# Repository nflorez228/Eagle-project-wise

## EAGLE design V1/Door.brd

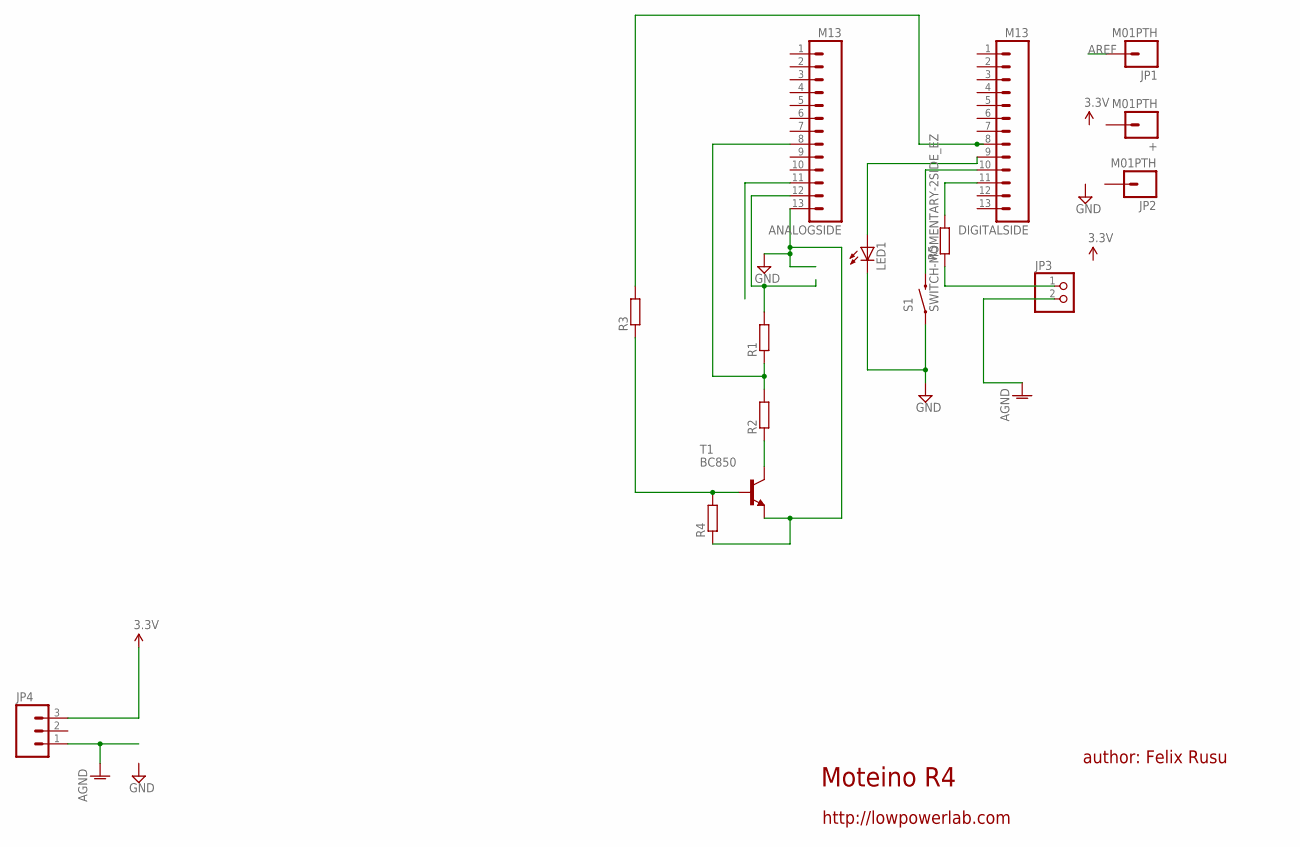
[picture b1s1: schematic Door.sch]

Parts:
+: M01PTH; 1X01
ANALOGSIDE: M13; 1X13
DIGITALSIDE: M13; 1X13
JP1, JP2: M01PTH; 1X01
JP3: PINHD-1X2; 1X02
JP4: M03PTH; 1X03
LED1: LED3MM
R1, R2, R5: R-EU_0204/7; 0204/7
R3, R4: R-EU_M1206; M1206
S1: SWITCH-MOMENTARY-2SIDE_EZ; TACTILE-PTH-SIDEEZ
T1: BC850; SOT23

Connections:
AGND: JP3.2, JP4.1
AREF: JP1.1
GND: ANALOGSIDE.13, LED1.K (C), R4.1, S1.1, T1.2 (E)
unnamed: DIGITALSIDE.10, S1.2
unnamed: JP3.1, R5.1
unnamed: DIGITALSIDE.9, LED1.A
unnamed: ANALOGSIDE.12, R1.2
unnamed: ANALOGSIDE.8, R1.1, R2.2
unnamed: R2.1, T1.3 (C)
unnamed: R3.1, R4.2, T1.1 (B)
unnamed: DIGITALSIDE.8, R3.2
unnamed: DIGITALSIDE.11, R5.2
VCC: JP4.3

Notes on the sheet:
Moteino R4
author: Felix Rusu
http://lowpowerlab.com

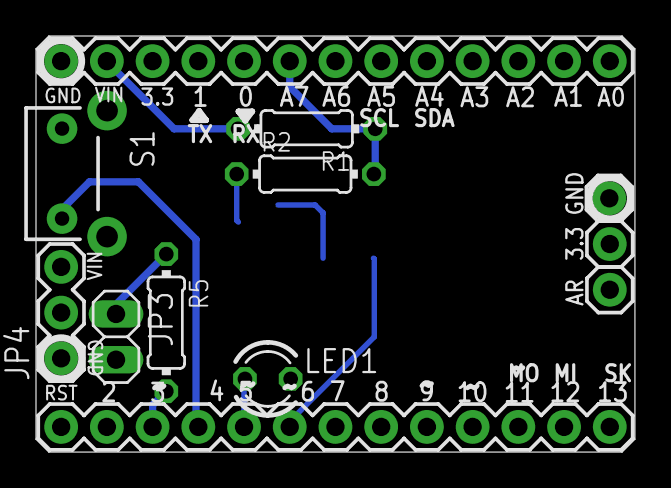
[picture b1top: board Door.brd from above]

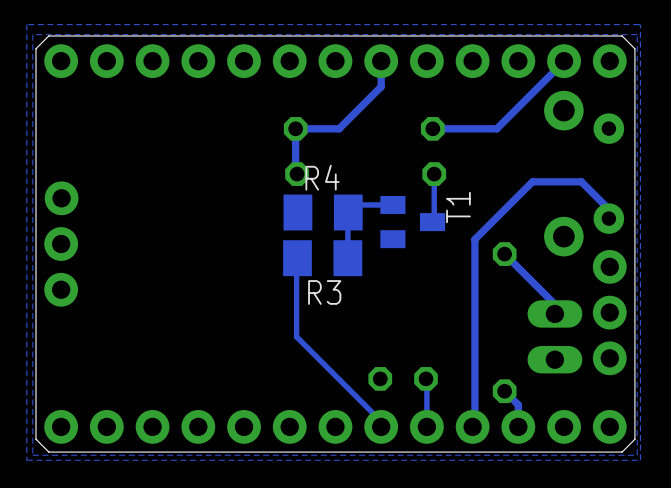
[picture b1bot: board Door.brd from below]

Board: 2 copper layers, 33.3 x 23.1 mm, 15 parts (3 on the bottom side), 11 nets.

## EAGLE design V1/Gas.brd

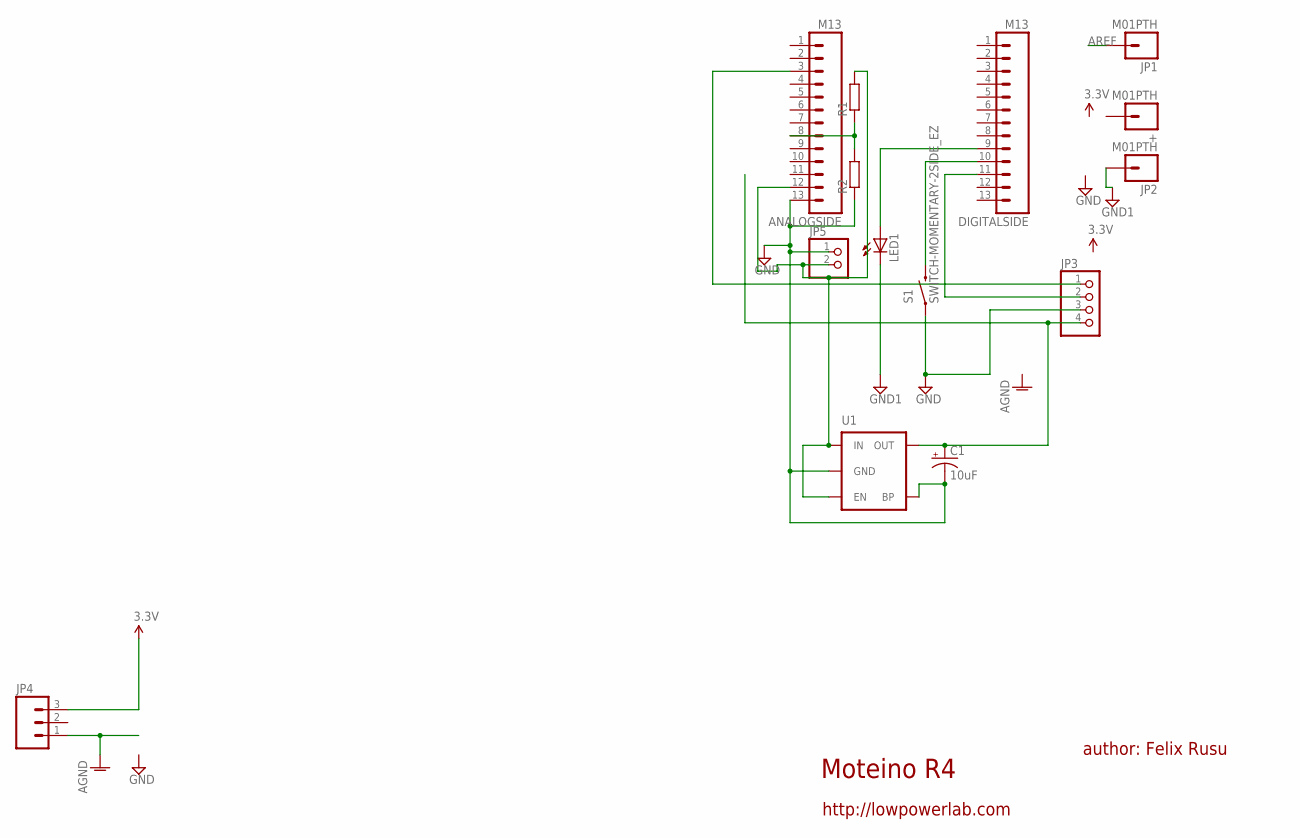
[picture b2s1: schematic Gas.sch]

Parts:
+: M01PTH; 1X01
ANALOGSIDE: M13; 1X13
C1: 10uF; EIA3216
DIGITALSIDE: M13; 1X13
JP1, JP2: M01PTH; 1X01
JP3: PINHD-1X4; 1X04
JP4: M03PTH; 1X03
JP5: PINHD-1X2; 1X02
LED1: LED3MM
R1, R2: R-EU_0204/7; 0204/7
S1: SWITCH-MOMENTARY-2SIDE_EZ; TACTILE-PTH-SIDEEZ
U1: MIC52055V; SOT23-5

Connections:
AGND: JP4.1
AREF: JP1.1
GND: ANALOGSIDE.13, C1.C (-), JP3.3, JP5.1, R2.1, S1.1, U1.2 (GND), U1.4 (BP)
GND1: JP2.1, LED1.K (C)
unnamed: DIGITALSIDE.10, S1.2
unnamed: DIGITALSIDE.11, JP3.2
unnamed: ANALOGSIDE.3, JP3.1
unnamed: ANALOGSIDE.12, JP5.2, R1.2, U1.1 (IN), U1.3 (EN)
unnamed: ANALOGSIDE.8, R1.1, R2.2
unnamed: DIGITALSIDE.9, LED1.A
unnamed: C1.A (+), JP3.4, U1.5 (OUT)
VCC: JP4.3

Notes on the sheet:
Moteino R4
author: Felix Rusu
http://lowpowerlab.com

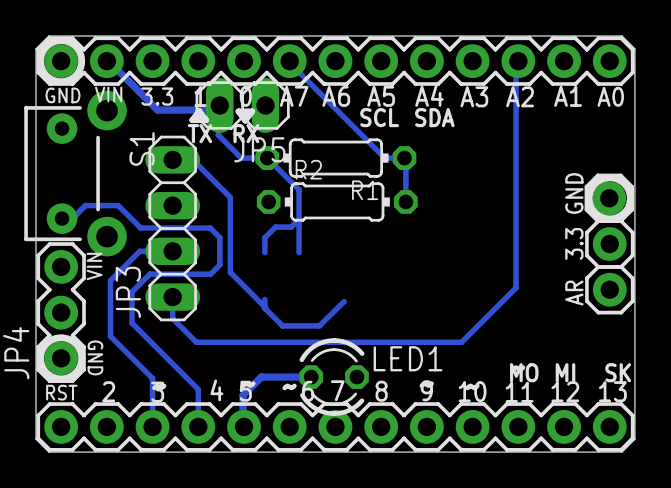
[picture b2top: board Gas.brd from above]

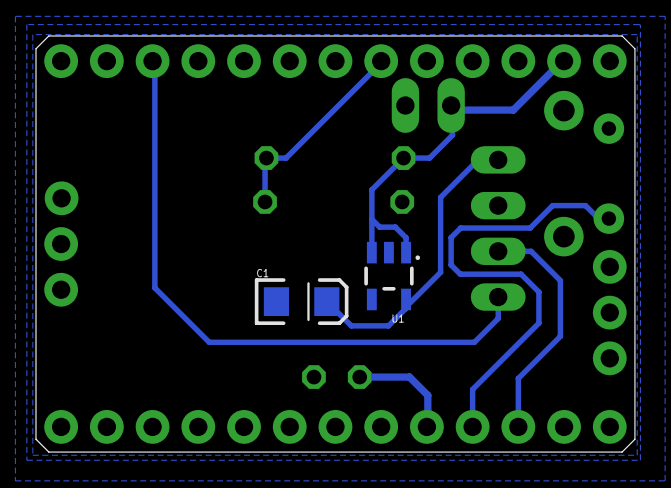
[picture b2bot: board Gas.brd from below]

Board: 2 copper layers, 33.3 x 23.1 mm, 14 parts (2 on the bottom side), 9 nets.

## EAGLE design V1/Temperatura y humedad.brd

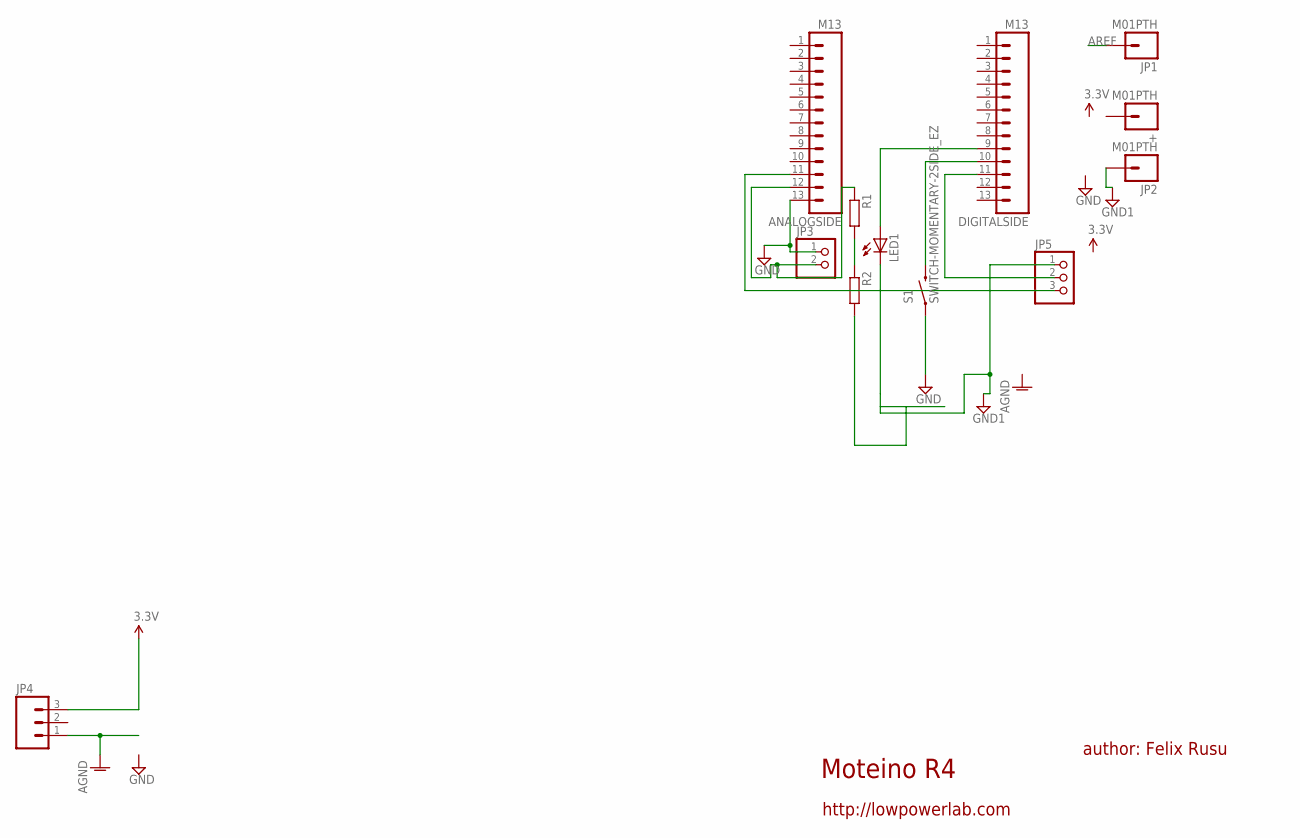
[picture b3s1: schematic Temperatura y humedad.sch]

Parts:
+: M01PTH; 1X01
ANALOGSIDE: M13; 1X13
DIGITALSIDE: M13; 1X13
JP1, JP2: M01PTH; 1X01
JP3: PINHD-1X2; 1X02
JP4: M03PTH; 1X03
JP5: PINHD-1X3; 1X03
LED1: LED3MM
R1, R2: R-EU_0204/7; 0204/7
S1: SWITCH-MOMENTARY-2SIDE_EZ; TACTILE-PTH-SIDEEZ

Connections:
AGND: JP4.1
AREF: JP1.1
GND: ANALOGSIDE.13, JP3.1, S1.1
GND1: JP2.1, JP5.1, LED1.K (C), R2.2
unnamed: DIGITALSIDE.10, S1.2
unnamed: DIGITALSIDE.11, JP5.2
unnamed: ANALOGSIDE.12, JP3.2, R1.1
unnamed: ANALOGSIDE.11, JP5.3
unnamed: DIGITALSIDE.9, LED1.A
unnamed: R1.2, R2.1
VCC: JP4.3

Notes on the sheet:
Moteino R4
author: Felix Rusu
http://lowpowerlab.com

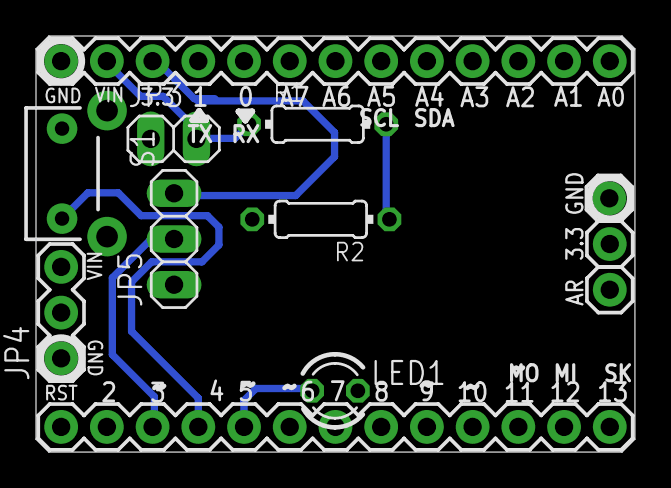
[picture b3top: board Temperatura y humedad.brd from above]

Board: 2 copper layers, 33.3 x 23.1 mm, 12 parts (0 on the bottom side), 8 nets.

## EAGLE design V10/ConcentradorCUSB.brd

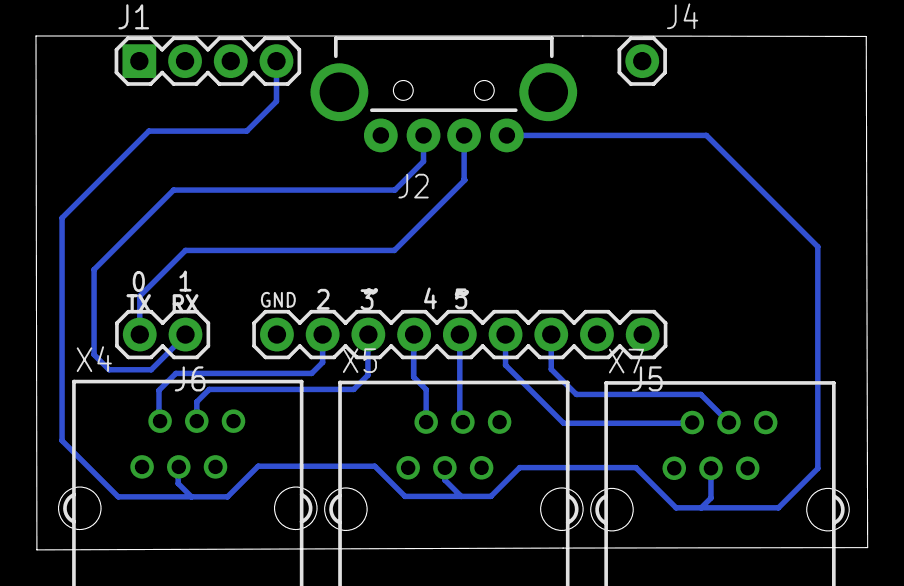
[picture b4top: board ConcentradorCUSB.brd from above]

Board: 2 copper layers, 46.2 x 28.5 mm, 8 parts (0 on the bottom side), 10 nets.

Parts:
J1: 1X04
J2: USB-A-H
J4: 1X01
J5: 1X09
J6: 1X02
X4, X5, X7: YH-55-10

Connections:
GND: J1.2, J2.VBUS, J5.9, X4.5, X5.5, X7.5
unnamed: J5.5, X5.4
unnamed: J5.6, X5.2
unnamed: J5.3, X7.4
unnamed: J2.D+, J6.2
unnamed: J5.4, X7.2
unnamed: J5.7, X4.4
unnamed: J5.8, X4.2
unnamed: J2.D-, J6.1
VIN: J1.4, J2.GND, X4.3, X5.3, X7.3

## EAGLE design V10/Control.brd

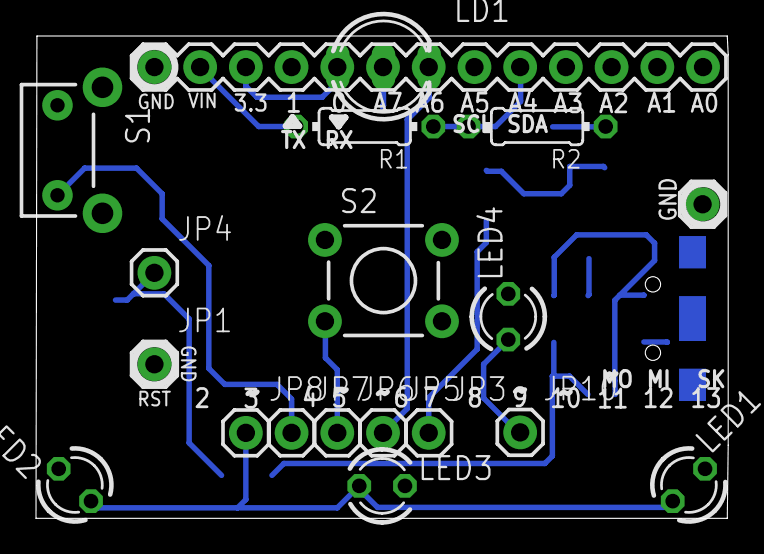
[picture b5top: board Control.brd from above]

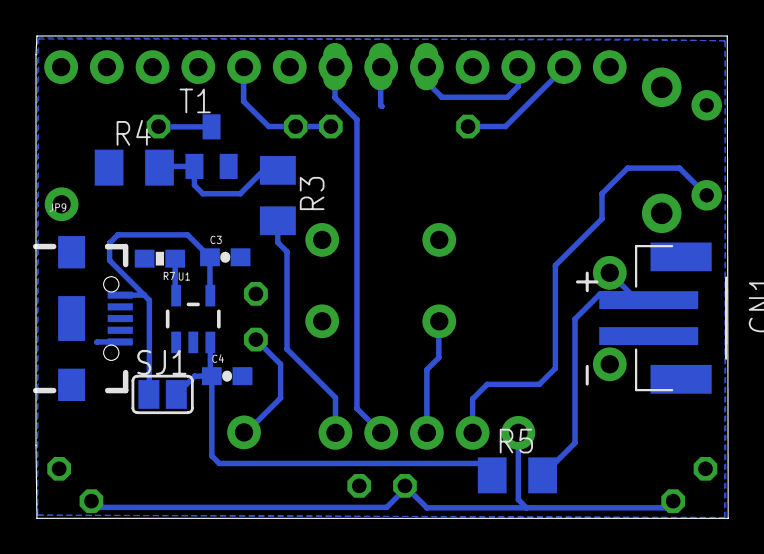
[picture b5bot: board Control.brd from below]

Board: 2 copper layers, 38.5 x 26.8 mm, 30 parts (11 on the bottom side), 17 nets.

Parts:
ANALOGSIDE: M13; 1X13
C3, C4: 4.7uF; 0603-CAP
CN1: JST-PH-2-SMT
JP1, JP2, JP3, JP4, JP5, JP6, JP7, JP8, JP10: M01PTH; 1X01
JP9: Micro USB; USB-AB-MICRO-SMD_V03
LD1: DUOLED-A-5MM
LED1, LED2, LED3, LED4: LED3MM
R1, R2: 0204/7
R3, R4, R5: M1206
R7: 2.0k; 0603-RES
S1: SWITCH-MOMENTARY-2SIDE_EZ; TACTILE-PTH-SIDEEZ
S2: TACTILE-PTH
SJ1: SJ
T1: BC850; SOT23
U1: MCP73831; SOT23-5

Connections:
AGND: CN1.2, JP1.1, LED2.K
GND: ANALOGSIDE.13, C3.2, C4.2, JP2.1, JP9.GND1, LD1.A, LED1.K, LED3.K, LED4.K, R4.1, R7.2, S1.1, S2.1, S2.2, T1.2, U1.2
unnamed: JP7.1, S1.2
unnamed: JP8.1, LED1.A, LED2.A, LED3.A
unnamed: JP6.1, S2.3
unnamed: JP5.1, LD1.CR
unnamed: C3.1, JP9.VBUS1, SJ1.1, U1.4
unnamed: ANALOGSIDE.5, R1.1, R2.2
unnamed: C4.1, R5.1, SJ1.2, U1.3
unnamed: ANALOGSIDE.12, R1.2
unnamed: JP3.1, R3.2
unnamed: R2.1, T1.3
unnamed: R3.1, R4.2, T1.1
unnamed: ANALOGSIDE.11, LD1.CX
unnamed: JP10.1, LED4.A
PROG: R7.1, U1.5
VCC: CN1.1, JP4.1, R5.2

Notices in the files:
parts and their libraries:
SparkFun-Connectors: Licensing: CC v3.0 Share-Alike You are welcome to use this library for commercial purposes.
SparkFun-Electromechanical: Licensing: Creative Commons ShareAlike 4.0 International - https://creativecommons.org/licenses/by-sa/4.0
